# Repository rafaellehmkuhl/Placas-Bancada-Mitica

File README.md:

# Placas-Bancada-Mitica

The *Bancada Mitica 2.0* eletronics use the concept of [Sensor Hubs](https://en.wikipedia.org/wiki/Sensor_hub), where there's one or more boards (called Sources) responsible for adquiring data from sensors, and there's one central board (called Sink) responsible for receiving data from Sources, processing and forwarding it.

This repository contains the schematic, board and gerber files for the boards used in the *Bancada Mitica 2.0* project.

Those Source boards currently include Load Cells (through HX711) and Pitots (through MPXV7002DP and ADS1115).

All boards were designed in Eagle 9 and exported for fabrication with Eagle 6.

*Connected PCBs*

*Pitot PCB*

*Pitot board project*

*LoadCell board project*

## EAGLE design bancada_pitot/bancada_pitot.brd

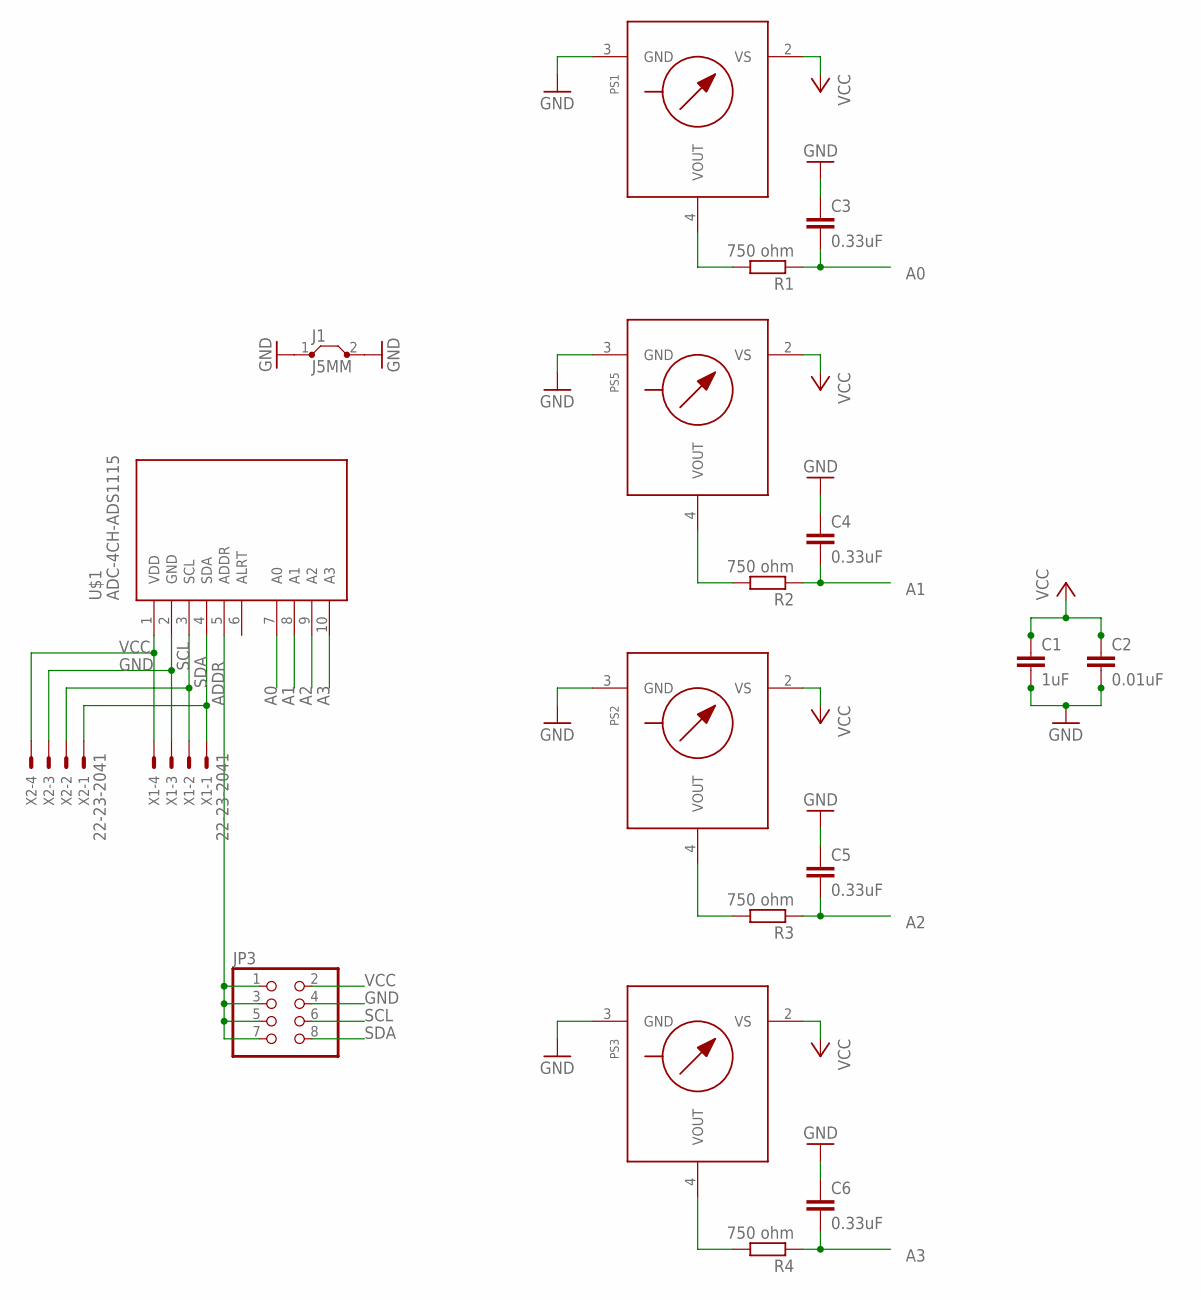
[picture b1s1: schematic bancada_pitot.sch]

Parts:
C1: 1uF; C025-025X050
C2: 0.01uF; C025-025X050
C3, C4, C5, C6: 0.33uF; C025-025X050
J1: J5MM; 05
JP3: PINHD-2X4; 2X04
PS1, PS2, PS3, PS5: MPX-1351; 1351
R1, R2, R3, R4: 750 ohm; 0207/2V
U$1: ADC-4CH-ADS1115
X1, X2: 22-23-2041

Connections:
A0: C3.2, R1.1, U$1.7 (A0)
A1: C4.2, R2.1, U$1.8 (A1)
A2: C5.2, R3.1, U$1.9 (A2)
A3: C6.2, R4.1, U$1.10 (A3)
ADDR: JP3.1, JP3.3, JP3.5, JP3.7, U$1.5 (ADDR)
GND: C1.2, C2.2, C3.1, C4.1, C5.1, C6.1, J1.1, J1.2, JP3.4, PS1.3 (GND), PS2.3 (GND), PS3.3 (GND), PS5.3 (GND), U$1.2 (GND), X1.3, X2.3
unnamed: PS1.4 (VOUT), R1.2
unnamed: PS5.4 (VOUT), R2.2
unnamed: PS2.4 (VOUT), R3.2
unnamed: PS3.4 (VOUT), R4.2
SCL: JP3.6, U$1.3 (SCL), X1.2, X2.2
SDA: JP3.8, U$1.4 (SDA), X1.1, X2.1
VCC: C1.1, C2.1, JP3.2, PS1.2 (VS), PS2.2 (VS), PS3.2 (VS), PS5.2 (VS), U$1.1 (VDD), X1.4, X2.4

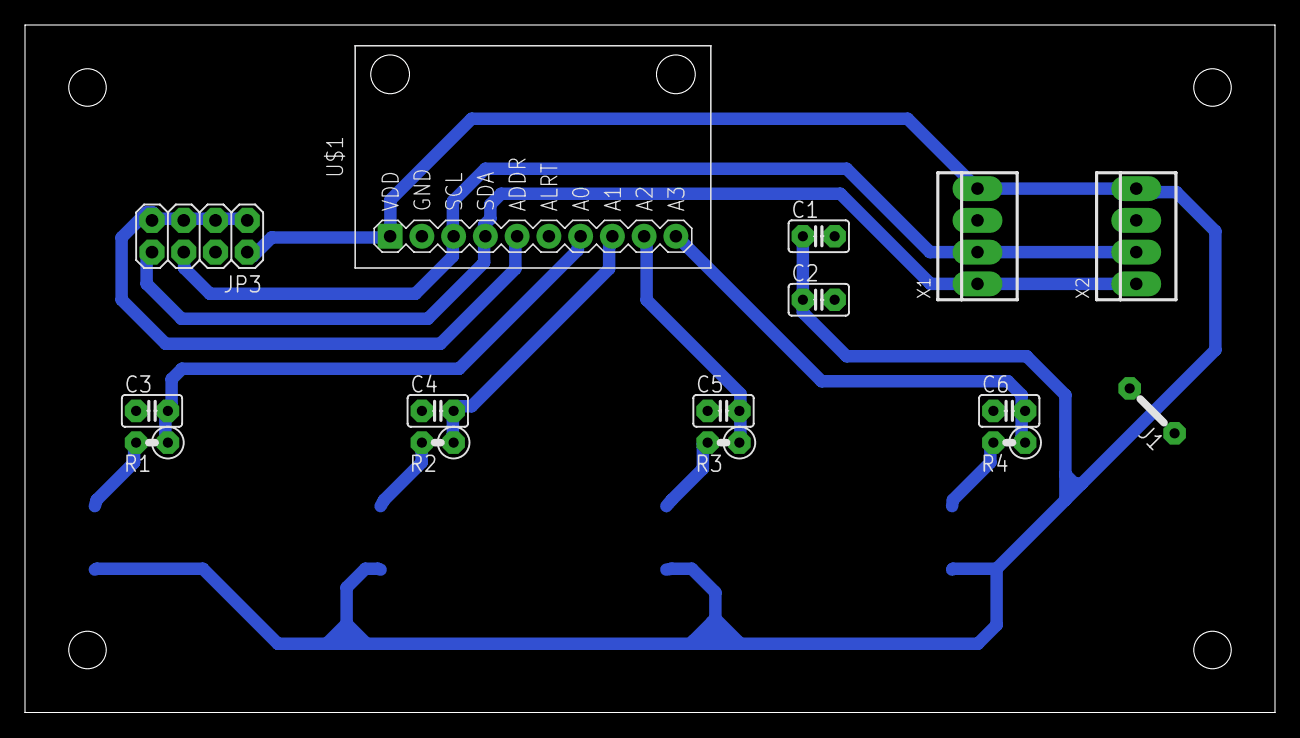
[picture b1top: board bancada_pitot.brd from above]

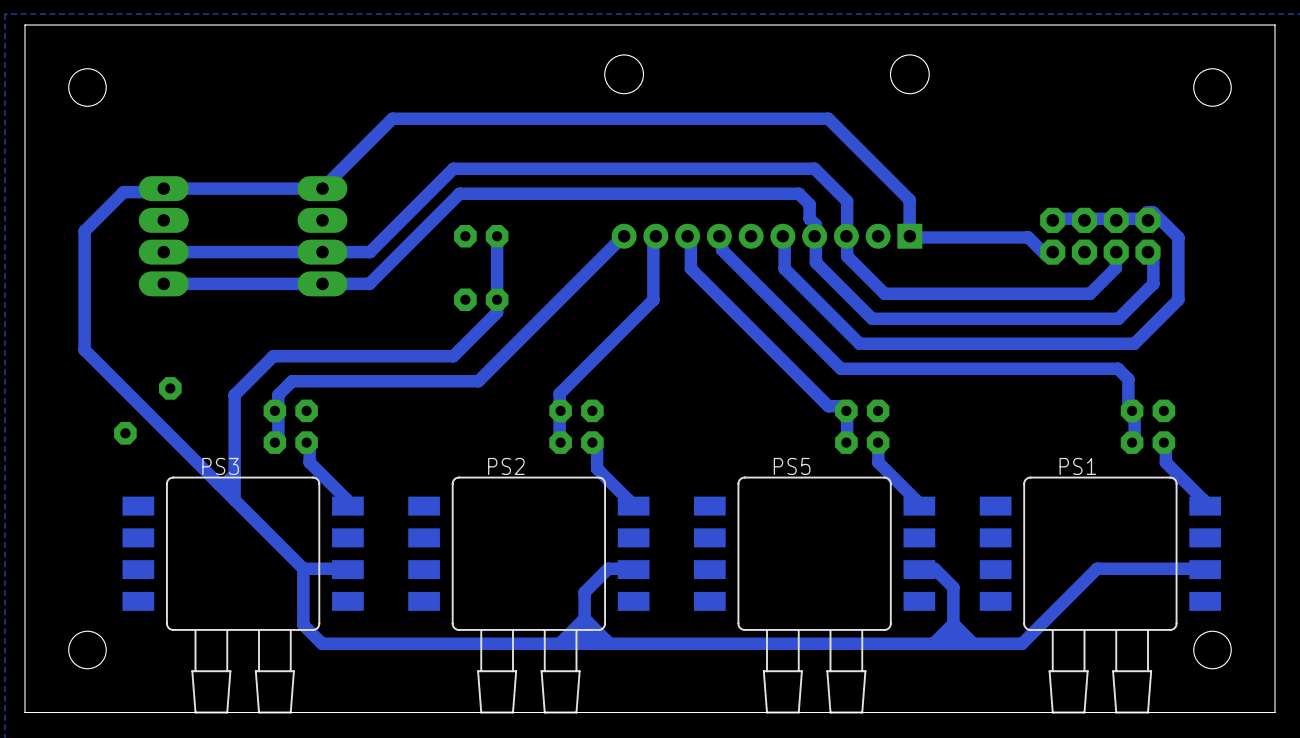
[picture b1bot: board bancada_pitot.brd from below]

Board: 2 copper layers, 100.0 x 55.0 mm, 19 parts (4 on the bottom side), 13 nets.

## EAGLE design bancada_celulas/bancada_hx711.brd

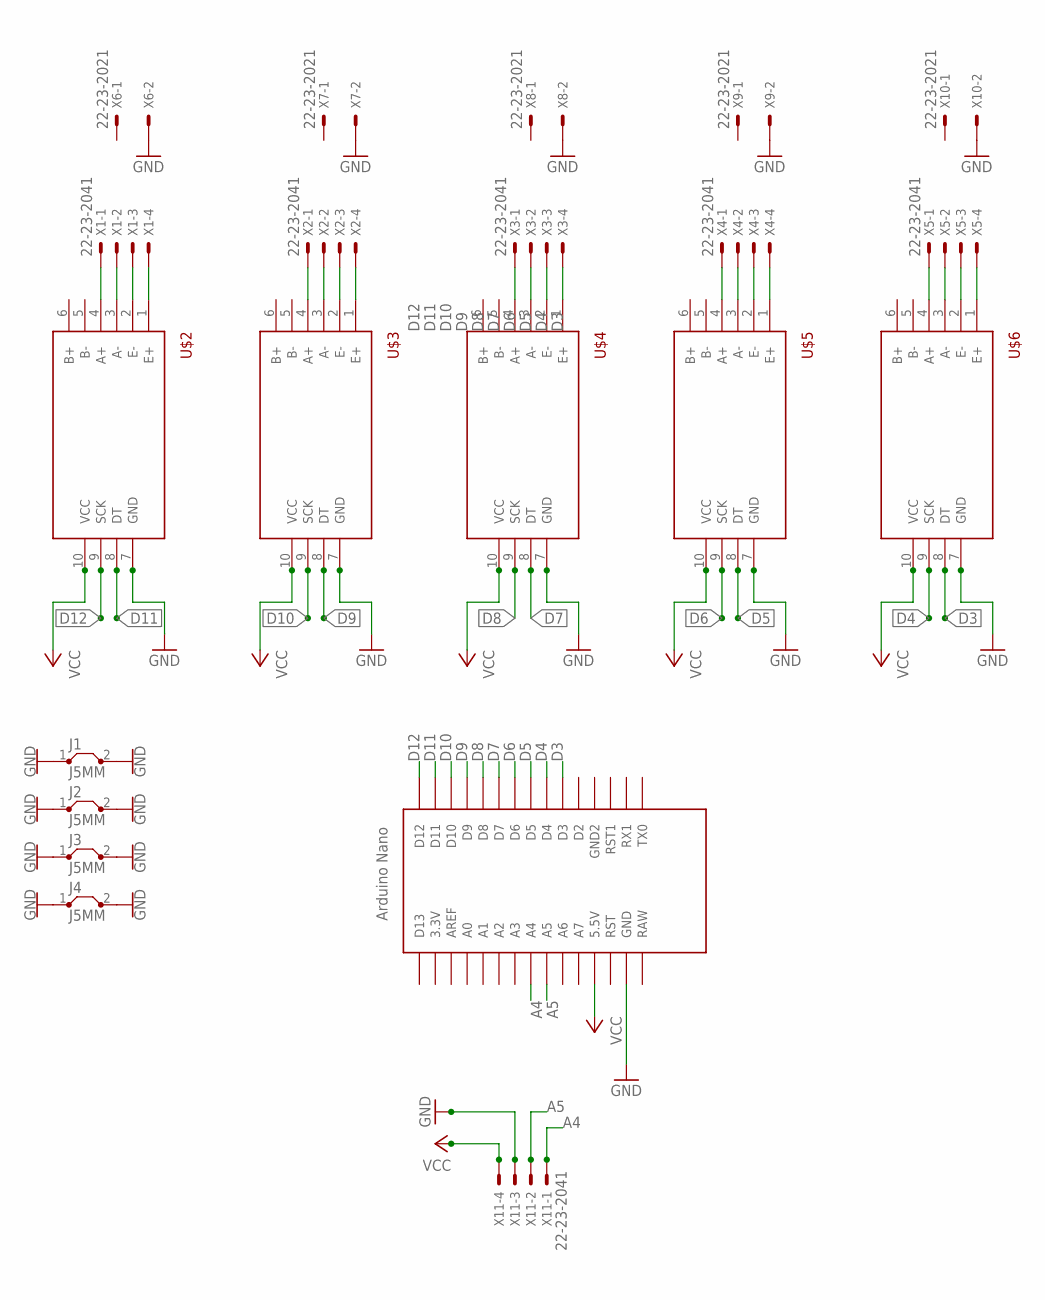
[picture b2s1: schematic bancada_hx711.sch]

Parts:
J1, J2, J3, J4: J5MM; 05
U$1: NANO
U$2, U$3, U$4, U$5, U$6: HX711-1
X1, X2, X3, X4, X5, X11: 22-23-2041
X6, X7, X8, X9, X10: 22-23-2021

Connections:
A4: U$1.A4, X11.1
A5: U$1.A5, X11.2
D3: U$1.D3, U$6.8 (DT)
D4: U$1.D4, U$6.9 (SCK)
D5: U$1.D5, U$5.8 (DT)
D6: U$1.D6, U$5.9 (SCK)
D7: U$1.D7, U$4.8 (DT)
D8: U$1.D8, U$4.9 (SCK)
D9: U$1.D9, U$3.8 (DT)
D10: U$1.D10, U$3.9 (SCK)
D11: U$1.D11, U$2.8 (DT)
D12: U$1.D12, U$2.9 (SCK)
GND: J1.1, J1.2, J2.1, J2.2, J3.1, J3.2, J4.1, J4.2, U$1.GND, U$2.7 (GND), U$3.7 (GND), U$4.7 (GND), U$5.7 (GND), U$6.7 (GND), X6.2, X7.2, X8.2, X9.2, X10.2, X11.3
unnamed: U$2.1 (E+), X1.4
unnamed: U$2.2 (E-), X1.3
unnamed: U$2.3 (A-), X1.2
unnamed: U$2.4 (A+), X1.1
unnamed: U$3.4 (A+), X2.1
unnamed: U$3.3 (A-), X2.2
unnamed: U$3.2 (E-), X2.3
unnamed: U$3.1 (E+), X2.4
unnamed: U$4.1 (E+), X3.4
unnamed: U$4.2 (E-), X3.3
unnamed: U$4.3 (A-), X3.2
unnamed: U$4.4 (A+), X3.1
unnamed: U$5.1 (E+), X4.4
unnamed: U$5.2 (E-), X4.3
unnamed: U$5.3 (A-), X4.2
unnamed: U$5.4 (A+), X4.1
unnamed: U$6.1 (E+), X5.4
unnamed: U$6.2 (E-), X5.3
unnamed: U$6.3 (A-), X5.2
unnamed: U$6.4 (A+), X5.1
VCC: U$1.5V (5.5V), U$2.10 (VCC), U$3.10 (VCC), U$4.10 (VCC), U$5.10 (VCC), U$6.10 (VCC), X11.4

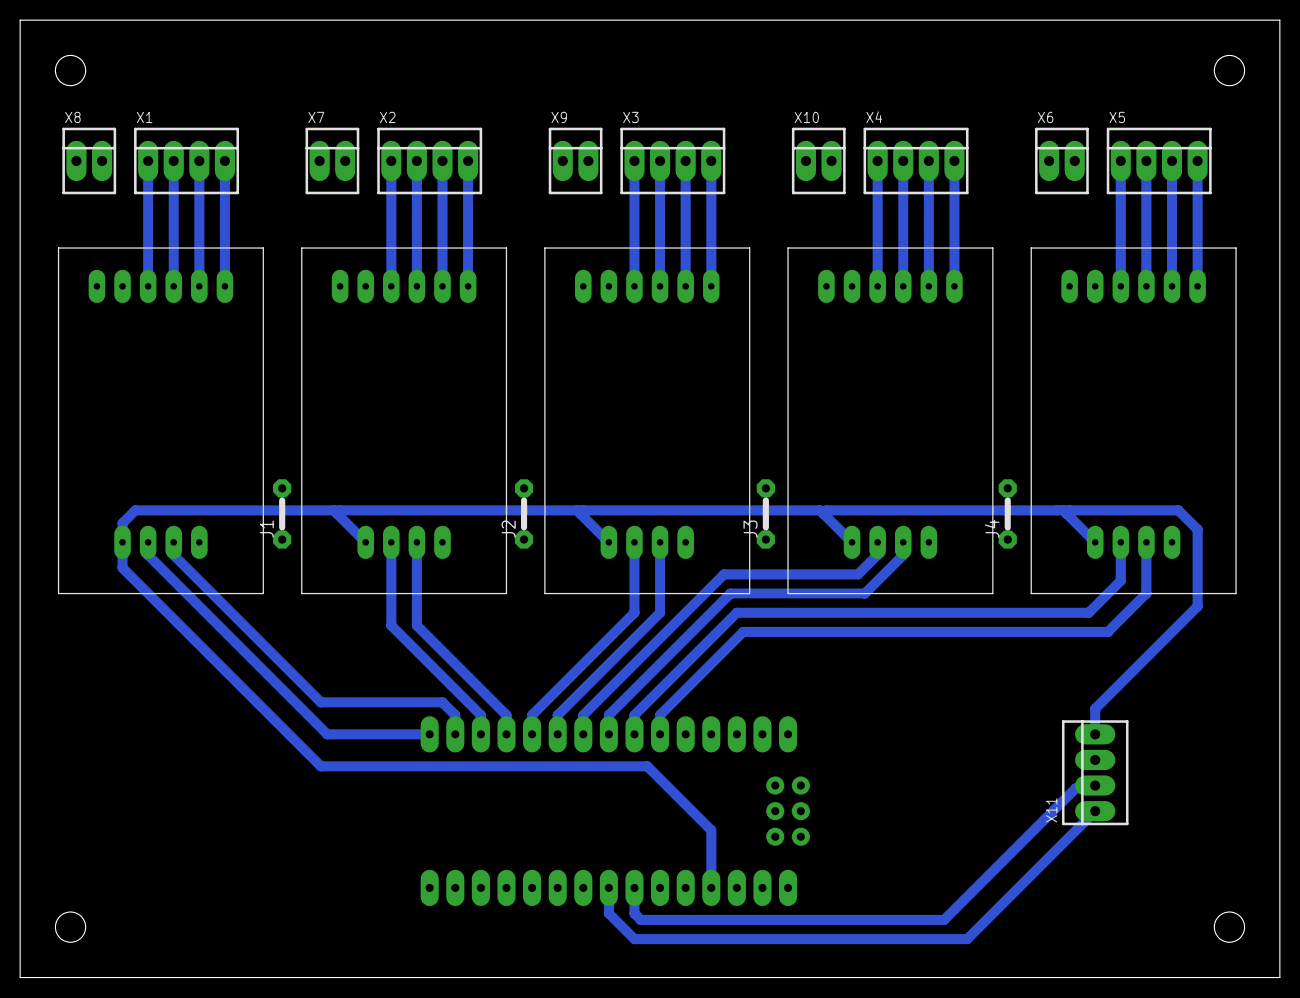
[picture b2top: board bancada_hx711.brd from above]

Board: 2 copper layers, 125.0 x 95.0 mm, 21 parts (0 on the bottom side), 34 nets.

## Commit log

2018-03-15 Add first version of pitot and nano/hx711 boards
2018-03-16 Correct the name for many files
2018-03-16 Generate new gerber and drill files
    Since Eagle v8 has a bug regarding the generation of gerber and drill files, those files were generated from Eagle v6. The new versions are here.
2018-03-22 KK connectors changed from 4mm to 2.54mm
2018-03-27 Increase the width of the grounded pins bridges and update DRC
    The connections between the GND pins and the GND plane were too thin, so on the milling process they ended up not connected.
    To solve this problem the width of those bridges were increased from 0.1016mm to 0.762mm changinf the GND polygon to 1.016mm width.
    A new DRC was created as is used by both boards.
2018-04-30 Name A4 and A5 lines
    A4 and A5 lines were hardwired. They are now named A4 and A5.
2018-04-30 Correct position for edge lines
    Both top and right edge lines were bad positioned, in a way that the four board holes were not the same distance from the edges. This makes dificult to position them on CAD files for posterior case m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
    Now the holes are 150mil apart from each edge.
2018-05-18 Add jumpers (or 0ohm resistors)
    In previous design, some ground planes were unconnected to each other. It was meant to be added jumper wires after production.
    This commit changes this to actual jumpers, with pins, so they don't need to be soldered from bottom, but can actually be placed on top, like any other through-hole component. 0ohm through-hole resis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
2018-05-18 Change board edges and holes
    Edges and holes are supossed to be in "mm", different from the components and traces, that should follow "mil" units.
    This way we the board respects the board manufacturer (who uses mil system) as well as the CAD designer (who uses metric system).
2018-05-18 Update README with description and images
    Update description and add images from boards.

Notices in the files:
parts and their libraries:
SparkFun-PowerSymbols: Licensing: Creative Commons ShareAlike 4.0 International - https://creativecommons.org/licenses/by-sa/4.0
diy_modules: Released under the Creative Commons Attribution 4.0 International License: http://creativecommons.org/licenses/by/4.0
